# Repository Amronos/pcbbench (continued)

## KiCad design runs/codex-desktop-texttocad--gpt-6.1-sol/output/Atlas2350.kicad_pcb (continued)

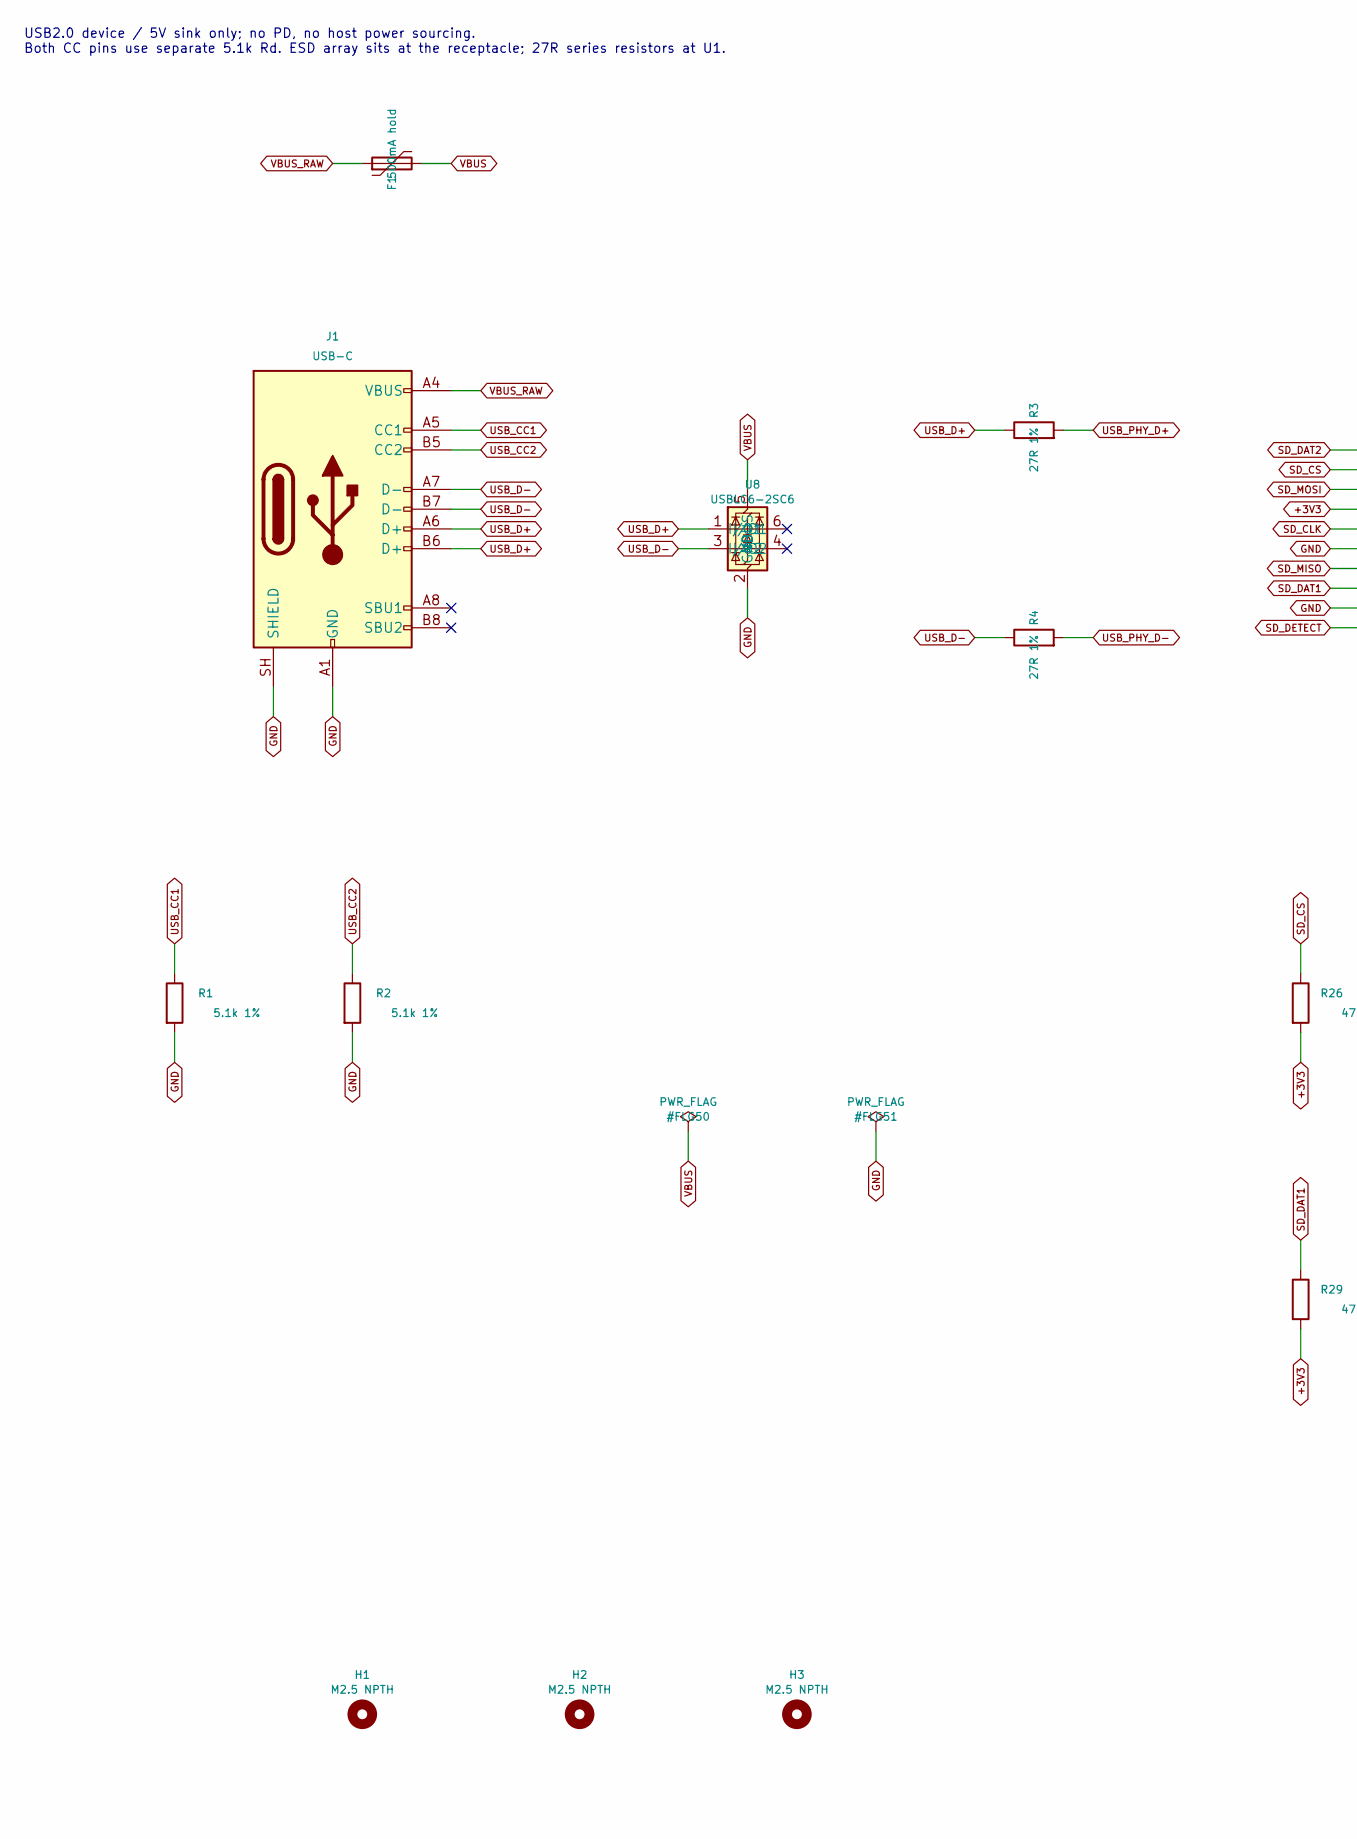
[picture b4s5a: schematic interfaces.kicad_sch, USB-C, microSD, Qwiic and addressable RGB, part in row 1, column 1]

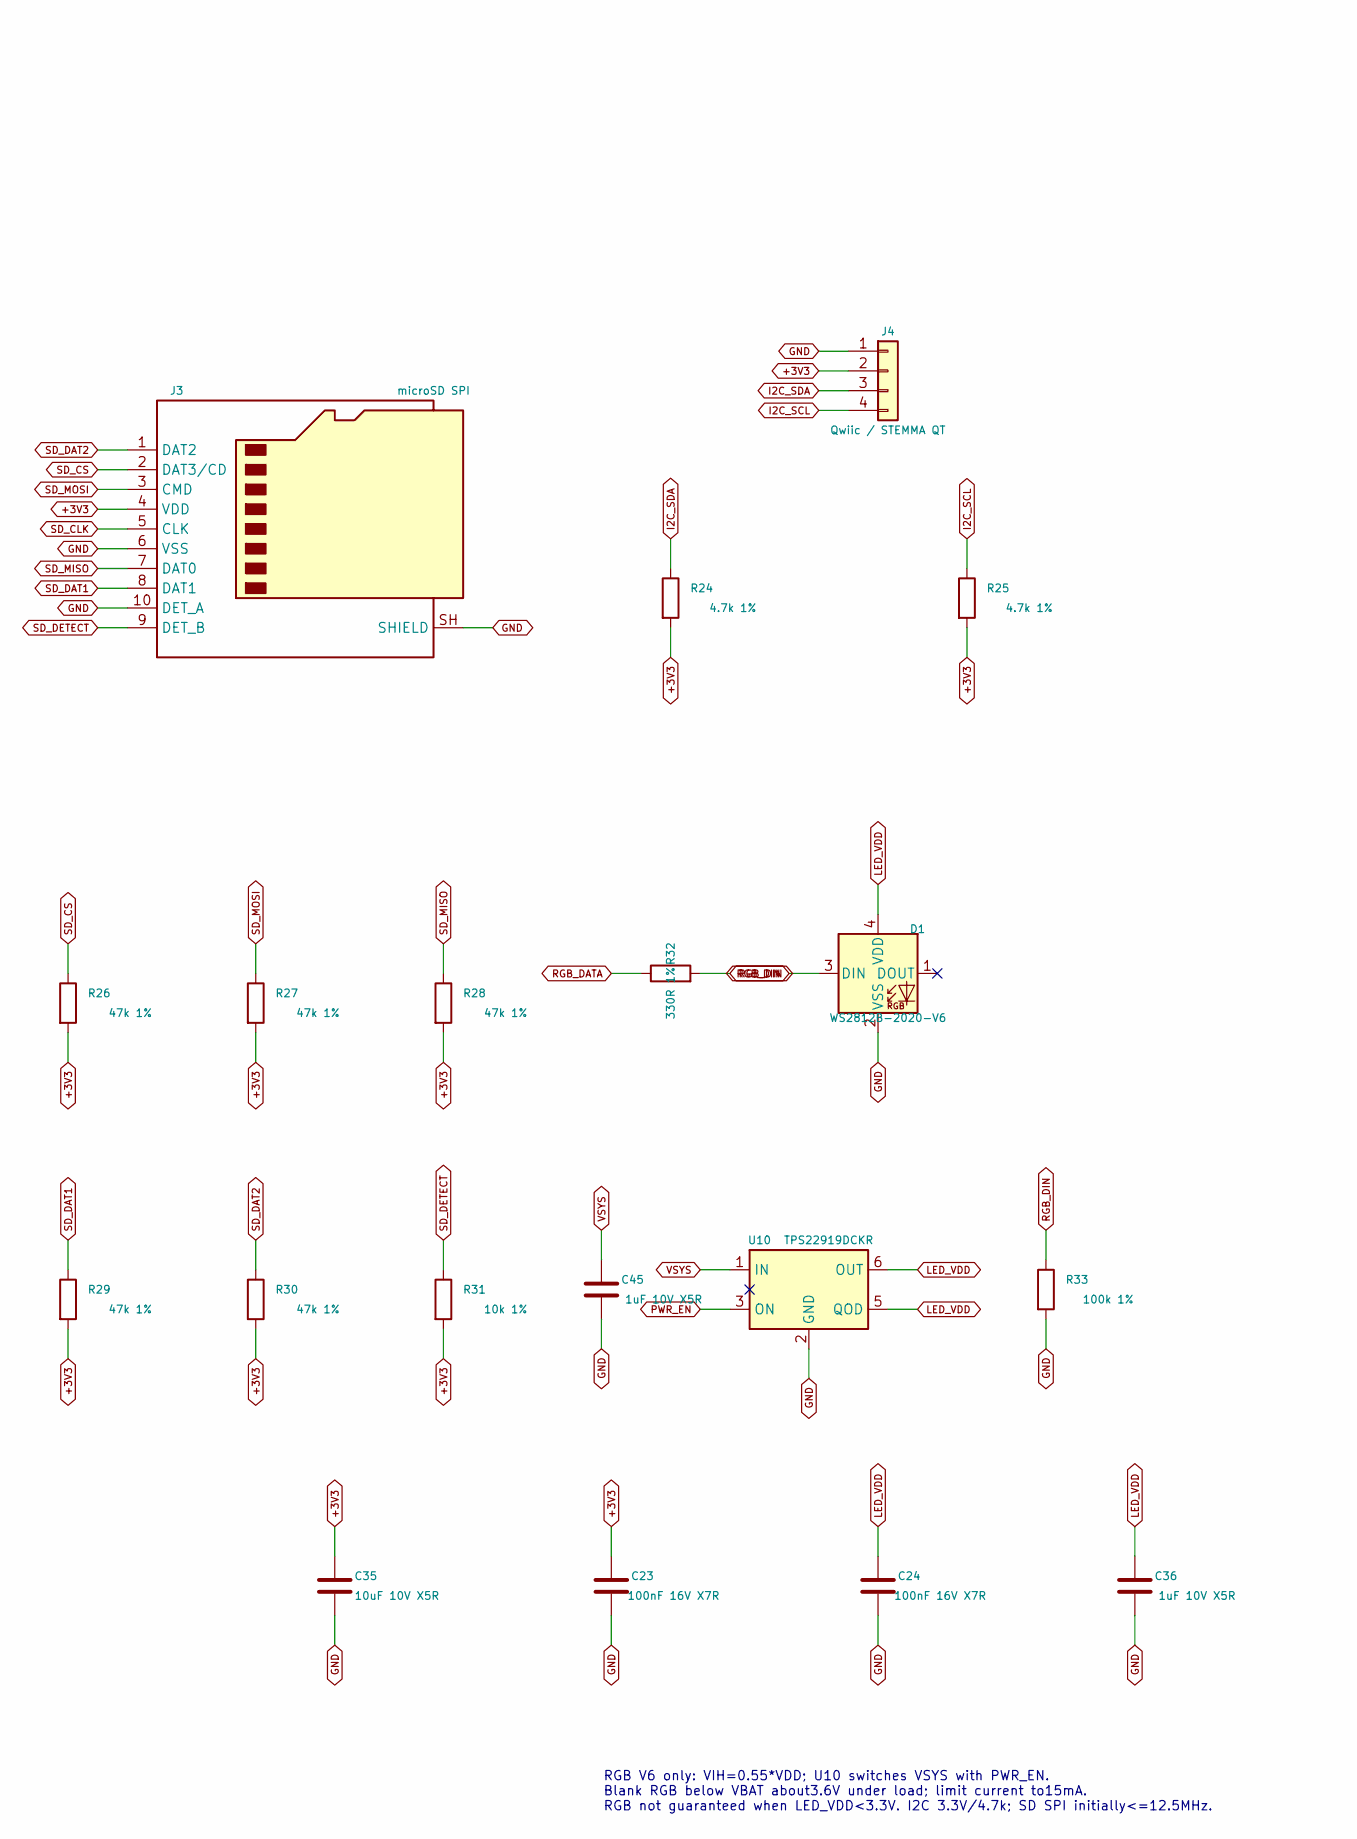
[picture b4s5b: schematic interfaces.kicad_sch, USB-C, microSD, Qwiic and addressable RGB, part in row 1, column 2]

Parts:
C23, C24: 100nF 16V X7R; Capacitor_SMD_C_0402_1005Metric; MPN GRM155R71C104KA88D
C35: 10uF 10V X5R; Capacitor_SMD_C_0805_2012Metric; MPN GRM21BR61A106KE19L
C36, C45: 1uF 10V X5R; Capacitor_SMD_C_0402_1005Metric; MPN GRM155R61A105KE15D
D1: WS2812B-2020-V6; LED_SMD_LED_WS2812B-2020_PLCC4_2.0x2.0mm; MPN WS2812B-2020-V6
F1: 500mA hold; Fuse_Fuse_1812_4532Metric; MPN MF-MSMF050-2
H1, H2, H3: M2.5 NPTH; MountingHole_MountingHole_2.7mm_M2.5
J1: USB-C; Connector_USB_USB_C_Receptacle_GCT_USB4105-xx-A_16P_TopMnt_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; MPN USB4105-GF-A
J3: microSD SPI; Connector_Card_microSD_HC_Hirose_DM3AT-SF-PEJM5; MPN DM3AT-SF-PEJM5
J4: Qwiic / STEMMA QT; Connector_JST_JST_SH_SM04B-SRSS-TB_1x04-1MP_P1.00mm_Horizon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; MPN SM04B-SRSS-TB(LF)(SN)
R1, R2: 5.1k 1%; Resistor_SMD_R_0402_1005Metric; MPN RC0402FR-075K1L
R3, R4: 27R 1%; Resistor_SMD_R_0402_1005Metric; MPN RC0402FR-0727RL
R24, R25: 4.7k 1%; Resistor_SMD_R_0402_1005Metric; MPN RC0402FR-074K7L
R26, R27, R28, R29, R30: 47k 1%; Resistor_SMD_R_0402_1005Metric; MPN RC0402FR-0747KL
R31: 10k 1%; Resistor_SMD_R_0402_1005Metric; MPN RC0402FR-0710KL
R32: 330R 1%; Resistor_SMD_R_0402_1005Metric; MPN RC0402FR-07330RL
R33: 100k 1%; Resistor_SMD_R_0402_1005Metric; MPN RC0402FR-07100KL
U8: USBLC6-2SC6; Package_TO_SOT_SMD_SOT-23-6; MPN USBLC6-2SC6
U10: TPS22919DCKR; Package_TO_SOT_SMD_SOT-363_SC-70-6; MPN TPS22919DCKR

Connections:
+3V3: C23.1, C35.1, J3.4 (VDD), J4.2, R24.2, R25.2, R26.2, R27.2, R28.2, R29.2, R30.2, R31.2; also elsewhere on the board
GND: C23.2, C24.2, C35.2, C36.2, C45.2, D1.2 (VSS), J1.A1 (GND), J1.A12 (GND), J1.B1 (GND), J1.B12 (GND), J1.SH (SHIELD), J3.6 (VSS), J3.10 (DET_A), J3.SH (SHIELD), J4.1, R1.2, R2.2, R33.2, U8.2 (GND), U10.2 (GND); also elsewhere on the board
I2C_SCL: J4.4, R25.1; also elsewhere on the board
I2C_SDA: J4.3, R24.1; also elsewhere on the board
LED_VDD: C24.1, C36.1, D1.4 (VDD), U10.5 (QOD), U10.6 (OUT)
PWR_EN: U10.3 (ON); also elsewhere on the board
RGB_DATA: R32.1; also elsewhere on the board
RGB_DIN: D1.3 (DIN), R32.2, R33.1
SD_CLK: J3.5 (CLK); also elsewhere on the board
SD_CS: J3.2 (DAT3/CD), R26.1; also elsewhere on the board
SD_DAT1: J3.8 (DAT1), R29.1
SD_DAT2: J3.1 (DAT2), R30.1
SD_DETECT: J3.9 (DET_B), R31.1; also elsewhere on the board
SD_MISO: J3.7 (DAT0), R28.1; also elsewhere on the board
SD_MOSI: J3.3 (CMD), R27.1; also elsewhere on the board
USB_CC1: J1.A5 (CC1), R1.1
USB_CC2: J1.B5 (CC2), R2.1
USB_D+: J1.A6 (D+), J1.B6 (D+), R3.1, U8.1 (I/O1)
USB_D-: J1.A7 (D-), J1.B7 (D-), R4.1, U8.3 (I/O2)
USB_PHY_D+: R3.2; also elsewhere on the board
USB_PHY_D-: R4.2; also elsewhere on the board
VBUS: F1.2, U8.5 (VBUS); also elsewhere on the board
VBUS_RAW: F1.1, J1.A4 (VBUS), J1.A9 (VBUS), J1.B4 (VBUS), J1.B9 (VBUS)
VSYS: C45.1, U10.1 (IN); also elsewhere on the board

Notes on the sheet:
USB2.0 device / 5V sink only; no PD, no host power sourcing. Both CC pins use separate 5.1k Rd. ESD array sits at the receptacle; 27R series resistors at U1.
RGB V6 only: VIH=0.55*VDD; U10 switches VSYS with PWR_EN. Blank RGB below VBAT about3.6V under load; limit current to15mA. RGB not guaranteed when LED_VDD<3.3V. I2C 3.3V/4.7k; SD SPI initially<=12.5MHz.

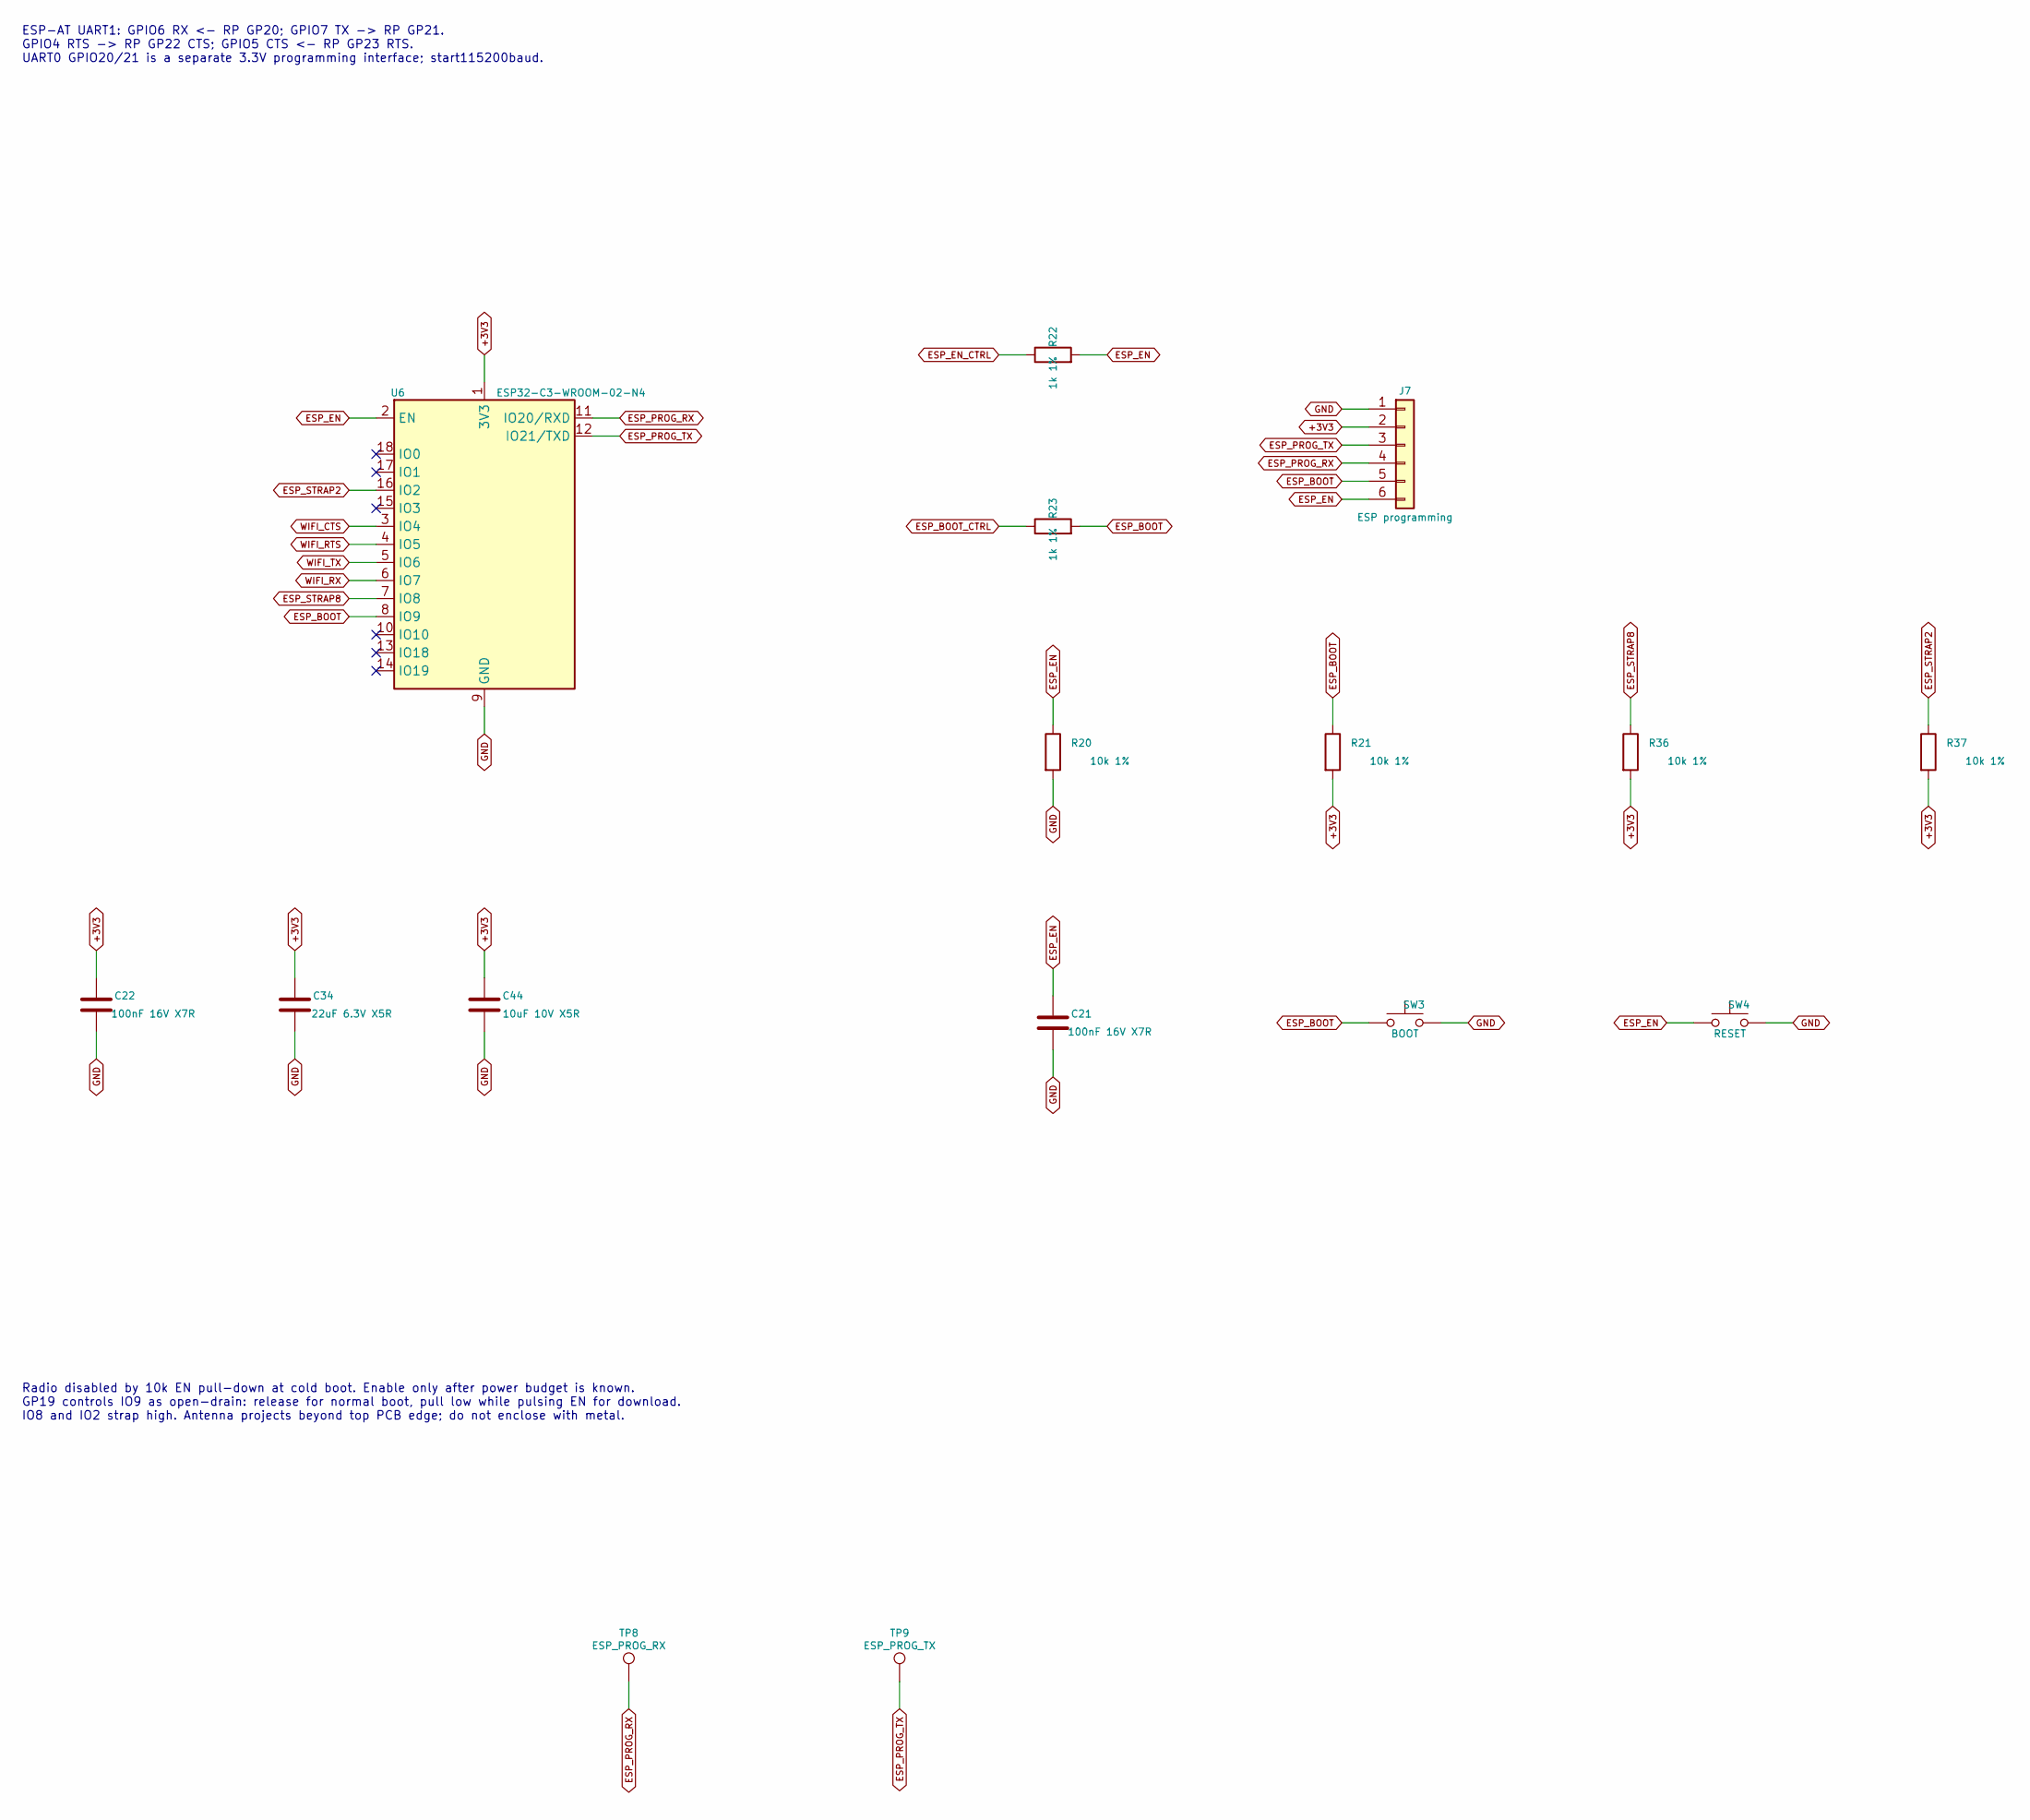
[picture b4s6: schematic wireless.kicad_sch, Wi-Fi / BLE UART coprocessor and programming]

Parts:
C21, C22: 100nF 16V X7R; Capacitor_SMD_C_0402_1005Metric; MPN GRM155R71C104KA88D
C34: 22uF 6.3V X5R; Capacitor_SMD_C_0805_2012Metric; MPN GRM21BR60J226ME39L
C44: 10uF 10V X5R; Capacitor_SMD_C_0805_2012Metric; MPN GRM21BR61A106KE19L
J7: ESP programming; Connector_PinHeader_2.54mm_PinHeader_1x06_P2.54mm_Vertical; MPN TSW-106-07-G-S
R20, R21, R36, R37: 10k 1%; Resistor_SMD_R_0402_1005Metric; MPN RC0402FR-0710KL
R22, R23: 1k 1%; Resistor_SMD_R_0402_1005Metric; MPN RC0402FR-071KL
SW3: BOOT; Button_Switch_SMD_SW_SPST_TL3342; MPN TL3342F160QG
SW4: RESET; Button_Switch_SMD_SW_SPST_TL3342; MPN TL3342F160QG
TP8: ESP_PROG_RX; TestPoint_TestPoint_Pad_D1.0mm
TP9: ESP_PROG_TX; TestPoint_TestPoint_Pad_D1.0mm
U6: ESP32-C3-WROOM-02-N4; RF_Module_ESP32-C3-WROOM-02; MPN ESP32-C3-WROOM-02-N4

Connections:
+3V3: C22.1, C34.1, C44.1, J7.2, R21.2, R36.2, R37.2, U6.1 (3V3); also elsewhere on the board
ESP_BOOT: J7.5, R21.1, R23.2, SW3.1, U6.8 (IO9)
ESP_BOOT_CTRL: R23.1; also elsewhere on the board
ESP_EN: C21.1, J7.6, R20.1, R22.2, SW4.1, U6.2 (EN)
ESP_EN_CTRL: R22.1; also elsewhere on the board
ESP_PROG_RX: J7.4, TP8.1 (1_1), U6.11 (IO20/RXD)
ESP_PROG_TX: J7.3, TP9.1 (1_1), U6.12 (IO21/TXD)
ESP_STRAP2: R37.1, U6.16 (IO2)
ESP_STRAP8: R36.1, U6.7 (IO8)
GND: C21.2, C22.2, C34.2, C44.2, J7.1, R20.2, SW3.2, SW4.2, U6.9 (GND), U6.19 (GND); also elsewhere on the board
WIFI_CTS: U6.3 (IO4); also elsewhere on the board
WIFI_RTS: U6.4 (IO5); also elsewhere on the board
WIFI_RX: U6.6 (IO7); also elsewhere on the board
WIFI_TX: U6.5 (IO6); also elsewhere on the board

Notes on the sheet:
ESP-AT UART1: GPIO6 RX <- RP GP20; GPIO7 TX -> RP GP21. GPIO4 RTS -> RP GP22 CTS; GPIO5 CTS <- RP GP23 RTS. UART0 GPIO20/21 is a separate 3.3V programming interface; start115200baud.
Radio disabled by 10k EN pull-down at cold boot. Enable only after power budget is known. GP19 controls IO9 as open-drain: release for normal boot, pull low while pulsing EN for download. IO8 and IO2 strap high. Antenna projects beyond top PCB edge; do not enclose with metal.

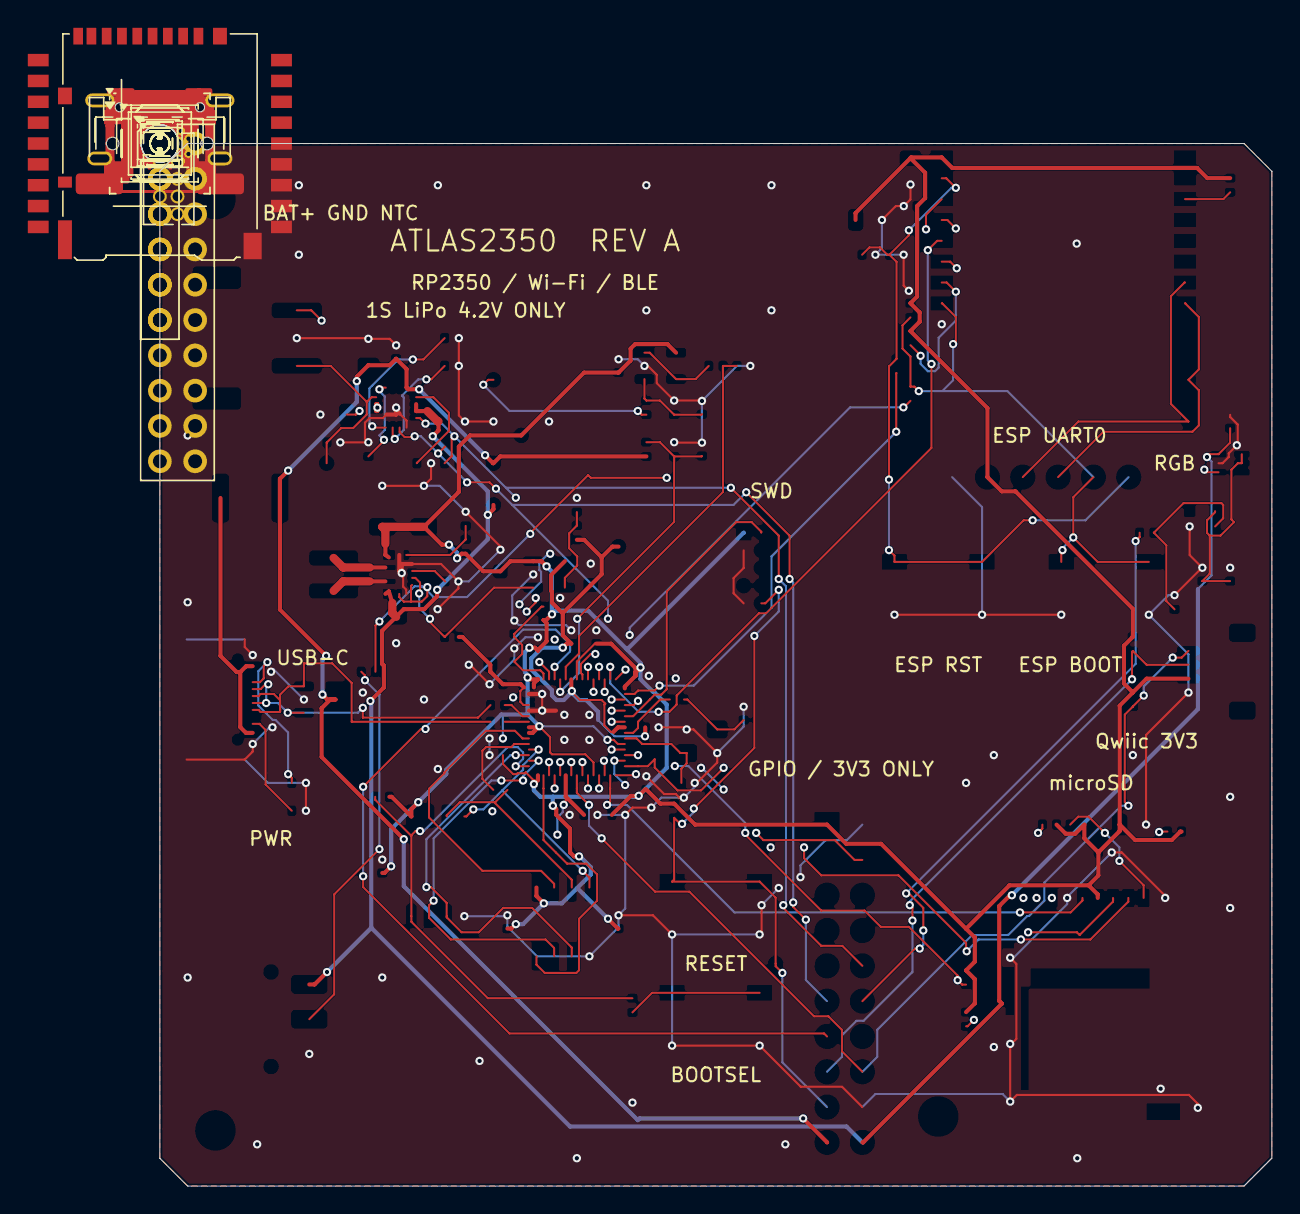
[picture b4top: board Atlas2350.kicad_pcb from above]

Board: 4 copper layers, 80.0 x 75.0 mm, 128 parts (0 on the bottom side), 81 nets.

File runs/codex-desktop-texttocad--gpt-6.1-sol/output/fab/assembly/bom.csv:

manufacturer,full_mpn,value,package,quantity,references,sides,mounting
Murata,GRM155R71C104KA88D,100nF 16V X7R,Atlas:Capacitor_SMD_C_0402_1005Metric,26,"C1, C2, C3, C4, C5, C6, C7, C8, C9, C10, C11, C12, C13, C14, C15, C16, C17, C18, C19, C20, C21, C22, C23, C24, C40, C42",top,SMT
Murata,GRM188R60J475KE19D,4.7uF 6.3V X5R,Atlas:Capacitor_SMD_C_0603_1608Metric,1,C25,top,SMT
Murata,GRM188R61A225KE15D,2.2uF 10V X5R,Atlas:Capacitor_SMD_C_0603_1608Metric,2,"C26, C27",top,SMT
Murata,GRM21BR61A106KE19L,10uF 10V X5R,Atlas:Capacitor_SMD_C_0805_2012Metric,5,"C28, C30, C31, C35, C44",top,SMT
Murata,GRM21BR61A475KA73L,4.7uF 10V X5R,Atlas:Capacitor_SMD_C_0805_2012Metric,1,C29,top,SMT
Murata,GRM31CR61C226KE15L,22uF 16V X5R,Atlas:Capacitor_SMD_C_1206_3216Metric,2,"C32, C33",top,SMT
Murata,GRM21BR60J226ME39L,22uF 6.3V X5R,Atlas:Capacitor_SMD_C_0805_2012Metric,1,C34,top,SMT
Murata,GRM155R61A105KE15D,1uF 10V X5R,Atlas:Capacitor_SMD_C_0402_1005Metric,4,"C36, C37, C43, C45",top,SMT
Murata,GRM1555C1H150JA01D,15pF 50V C0G,Atlas:Capacitor_SMD_C_0402_1005Metric,2,"C38, C39",top,SMT
Murata,GRM1555C1H102JA01D,1nF 50V C0G,Atlas:Capacitor_SMD_C_0402_1005Metric,1,C41,top,SMT
Worldsemi,WS2812B-2020-V6,WS2812B-2020-V6,Atlas:LED_SMD_LED_WS2812B-2020_PLCC4_2.0x2.0mm,1,D1,top,SMT
Bourns,MF-MSMF050-2,500mA hold,Atlas:Fuse_Fuse_1812_4532Metric,1,F1,top,SMT
Murata,BLM15AG601SN1D,600R @ 100MHz,Atlas:Inductor_SMD_L_0402_1005Metric,1,FB1,top,SMT
GCT,USB4105-GF-A,USB-C,Atlas:Connector_USB_USB_C_Receptacle_GCT_USB4105-xx-A_16P_TopMnt_Horizontal,1,J1,top,SMT+THT
JST,S3B-PH-SM4-TB(LF)(SN),LiPo + NTC,Atlas:Connector_JST_JST_PH_S3B-PH-SM4-TB_1x03-1MP_P2.00mm_Horizontal,1,J2,top,SMT
Hirose,DM3AT-SF-PEJM5,microSD SPI,Atlas:Connector_Card_microSD_HC_Hirose_DM3AT-SF-PEJM5,1,J3,top,SMT
JST,SM04B-SRSS-TB(LF)(SN),Qwiic / STEMMA QT,Atlas:Connector_JST_JST_SH_SM04B-SRSS-TB_1x04-1MP_P1.00mm_Horizontal,1,J4,top,SMT
Samtec,TSW-110-07-G-D,GPIO expansion,Atlas:Connector_PinHeader_2.54mm_PinHeader_2x10_P2.54mm_Vertical,1,J5,top,THT
Samtec,FTSH-105-01-L-D,Cortex SWD,Atlas:Connector_PinHeader_1.27mm_PinHeader_2x05_P1.27mm_Vertical,1,J6,top,THT
Samtec,TSW-106-07-G-S,ESP programming,Atlas:Connector_PinHeader_2.54mm_PinHeader_1x06_P2.54mm_Vertical,1,J7,top,THT
Coilcraft,XAL4020-102MEC,1.0uH,Atlas:Inductor_SMD_L_Coilcraft_XAL4020-XXX,1,L1,top,SMT
Yageo,RC0402FR-075K1L,5.1k 1%,Atlas:Resistor_SMD_R_0402_1005Metric,2,"R1, R2",top,SMT
Yageo,RC0402FR-0727RL,27R 1%,Atlas:Resistor_SMD_R_0402_1005Metric,2,"R3, R4",top,SMT
Yageo,RC0402FR-073K57L,3.57k 1%,Atlas:Resistor_SMD_R_0402_1005Metric,1,R5,top,SMT
Yageo,RC0402FR-073K24L,3.24k 1%,Atlas:Resistor_SMD_R_0402_1005Metric,1,R6,top,SMT
Yageo,RC0402FR-07100KL,100k 1%,Atlas:Resistor_SMD_R_0402_1005Metric,3,"R7, R33, R41",top,SMT
Yageo,RC0402FR-0710KL,10k 1%,Atlas:Resistor_SMD_R_0402_1005Metric,11,"R8, R9, R14, R15, R18, R20, R21, R31, R36, R37, R40",top,SMT
Yageo,RC0402FR-07470KL,470k 1%,Atlas:Resistor_SMD_R_0402_1005Metric,2,"R10, R11",top,SMT
Yageo,RC0402FR-071ML,1M 1%,Atlas:Resistor_SMD_R_0402_1005Metric,1,R12,top,SMT
Yageo,RC0402FR-07330KL,330k 1%,Atlas:Resistor_SMD_R_0402_1005Metric,1,R13,top,SMT
Yageo,RC0402FR-0733RL,33R 1%,Atlas:Resistor_SMD_R_0402_1005Metric,1,R16,top,SMT
Yageo,RC0402FR-071KL,1k 1%,Atlas:Resistor_SMD_R_0402_1005Metric,5,"R17, R19, R22, R23, R39",top,SMT
Yageo,RC0402FR-074K7L,4.7k 1%,Atlas:Resistor_SMD_R_0402_1005Metric,2,"R24, R25",top,SMT
Yageo,RC0402FR-0747KL,47k 1%,Atlas:Resistor_SMD_R_0402_1005Metric,5,"R26, R27, R28, R29, R30",top,SMT
Yageo,RC0402FR-07330RL,330R 1%,Atlas:Resistor_SMD_R_0402_1005Metric,1,R32,top,SMT
Yageo,RT0402BRD0710KL,10k 0.1%,Atlas:Resistor_SMD_R_0402_1005Metric,2,"R34, R35",top,SMT
Yageo,RC0402FR-07100RL,100R 1%,Atlas:Resistor_SMD_R_0402_1005Metric,1,R38,top,SMT
Yageo,RT0402BRD07312KL,312k 0.1%,Atlas:Resistor_SMD_R_0402_1005Metric,1,R42,top,SMT
Yageo,RT0402BRD07100KL,100k 0.1%,Atlas:Resistor_SMD_R_0402_1005Metric,1,R43,top,SMT
E-Switch,TL3342F160QG,RESET,Atlas:Button_Switch_SMD_SW_SPST_TL3342,2,"SW1, SW4",top,SMT
E-Switch,TL3342F160QG,BOOT,Atlas:Button_Switch_SMD_SW_SPST_TL3342,2,"SW2, SW3",top,SMT
C&K,JS102011SAQN,POWER,Atlas:Button_Switch_SMD_SW_SPDT_CK_JS102011SAQN,1,SW5,top,SMT
Raspberry Pi,RP2350A,RP2350A,Atlas:Package_DFN_QFN_QFN-60-1EP_7x7mm_P0.4mm_EP3.4x3.4mm,1,U1,top,SMT
Winbond,W25Q32JVSSIQ,W25Q32JVSSIQ,Atlas:Package_SO_SOIC-8_5.3x5.3mm_P1.27mm,1,U2,top,SMT
AP Memory,APS6404L-3SQR-SN,APS6404L-3SQR-SN,Atlas:Package_SO_SOIC-8_3.9x4.9mm_P1.27mm,1,U3,top,SMT
Texas Instruments,BQ24074RGTR,BQ24074RGTR,Atlas:Package_DFN_QFN_VQFN-16-1EP_3x3mm_P0.5mm_EP1.6x1.6mm,1,U4,top,SMT
Texas Instruments,TPS63070RNMR,TPS63070RNMR,Atlas:Custom_TPS63070_RNM0015A,1,U5,top,SMT
Espressif Systems,ESP32-C3-WROOM-02-N4,ESP32-C3-WROOM-02-N4,Atlas:RF_Module_ESP32-C3-WROOM-02,1,U6,top,SMT with plated thermal features
Texas Instruments,TLV75801PDBVR,TLV75801PDBVR,Atlas:Package_TO_SOT_SMD_SOT-23-5,1,U7,top,SMT
STMicroelectronics,USBLC6-2SC6,USBLC6-2SC6,Atlas:Package_TO_SOT_SMD_SOT-23-6,1,U8,top,SMT
Texas Instruments,TLV9001IDBVR,TLV9001IDBVR,Atlas:Package_TO_SOT_SMD_SOT-23-5,1,U9,top,SMT
Texas Instruments,TPS22919DCKR,TPS22919DCKR,Atlas:Package_TO_SOT_SMD_SOT-363_SC-70-6,1,U10,top,SMT
Abracon,ABM8-272-T3,12MHz / 10pF,Atlas:Crystal_Crystal_SMD_Abracon_ABM8G-4Pin_3.2x2.5mm,1,Y1,top,SMT
